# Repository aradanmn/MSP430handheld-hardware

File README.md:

# Handheld MSP430 — Hardware

Hardware design for a DIY handheld game console built around the
**MSP430G2553** microcontroller: bill of materials, breadboard layout, KiCad 9
schematic, and the engineering design history.

This repo is the **hardware side** of the project. The firmware and the
26-lesson MSP430 assembly course that builds it live in the companion
software repo: **[aradanmn/MSP430handheld-firmware](https://github.com/aradanmn/MSP430handheld-firmware)**.

## Components

| Component | Part | Purpose |
|-----------|------|---------|
| MCU | MSP430G2553 (LaunchPad MSP-EXP430G2) | Main controller |
| Display | SSD1325 2.7″ OLED, 128×64 grayscale SPI | Video output |
| SRAM | 23LC1024-I/P (128 KB SPI, DIP-8) | Off-chip framebuffer backing store |
| Flash | W25Q128 (16 MB SPI, DIP breakout, Adafruit #5634) | Asset / level storage |
| Shift register | SN74HC165N (DIP-16) | 8-button input over the SPI bus |
| Audio amp | LM386N-1 (DIP-8) | PWM → speaker |
| Speaker | SP-3605, 8 Ω | Audio output |
| LiPo charger | Adafruit 4410 (USB-C) | Battery charging |
| Battery | Adafruit 2011 (3.7 V LiPo, JST-PH) | Power |

Full ordering detail: [`bom-structured.md`](bom-structured.md),
[`bom-flat.md`](bom-flat.md), [`bom-order.csv`](bom-order.csv).

## Bus & pins

All SPI peripherals share the MSP430's **USCI_B0** bus and are selected by
individual chip-select lines (only one CS low at a time):

| Signal | MSP430 pin |
|--------|-----------|
| SCLK | P1.5 (UCB0CLK) |
| MOSI | P1.7 (UCB0SIMO) |
| MISO | P1.6 (UCB0SOMI) |

The authoritative per-signal chip-select and control assignments (rev 5.0) are
in the schematic `title_block` of
[`schematic/msp430_gameboy.kicad_sch`](schematic/msp430_gameboy.kicad_sch),
and the per-phase wiring is broken out under [`wiring/`](wiring/).

## Repository layout

```
MSP430handheld-hardware/
├── bom-flat.md / bom-structured.md / bom-order.csv   Bill of materials
├── schematic/     KiCad 9 schematic (rev 5.0) + timestamped snapshots
├── breadboard/    Elenco 9440 layout — breadboard_layout.html + breadboard_guide.md
├── scripts/       Schematic generators — gen_kicad7.py (current), gen_kicad6.py (prior)
├── wiring/        Per-build-phase wiring guides (phase-1 … phase-4)
├── DESIGN.md      Handheld rev A: carrier PCB + enclosure design, assumptions to check
├── pcb/           Carrier PCB generator, KiCad board, gerbers/drill/DXF/STEP, DRC report
├── enclosure/     Parametric OpenSCAD enclosure + STLs
├── datasheets/    Component datasheets + pin-function reference (see its README)
├── notes/         Versioned engineering notes (yyyymmdd_HHmmss.md) + SESSION_NOTES.md
└── logs/          Session conversation logs
```

## Build phases

Hardware is added incrementally as the course progresses:

- [`wiring/phase-1-launchpad-only.md`](wiring/phase-1-launchpad-only.md) — bare LaunchPad (Lessons 1–5)
- [`wiring/phase-2-oled-display.md`](wiring/phase-2-oled-display.md) — OLED + SRAM + Flash on the SPI bus
- [`wiring/phase-3-buttons-shift-register.md`](wiring/phase-3-buttons-shift-register.md) — 8-button SN74HC165N input
- [`wiring/phase-4-audio.md`](wiring/phase-4-audio.md) — LM386 amplifier + speaker

## Schematic

The KiCad 9 schematic is generated programmatically rather than drawn by hand.

```bash
python3 scripts/gen_kicad7.py     # writes schematic/msp430_gameboy.kicad_sch
```

Optional validation: `pip install kiutils`.

- **PCB (rev 6.0):** [`schematic/msp430_handheld.kicad_sch`](schematic/msp430_handheld.kicad_sch) / [PDF](schematic/msp430_handheld.pdf), MSP430G2553 on board, written by `scripts/gen_schematic.py` as part of `pcb/build.sh`
- Breadboard (rev 5.0): [`schematic/msp430_gameboy.kicad_sch`](schematic/msp430_gameboy.kicad_sch) — rev 5.0 (adds OLED CS/DC/RST, SRAM, Flash)
- Generator: [`scripts/gen_kicad7.py`](scripts/gen_kicad7.py) (current), `scripts/gen_kicad6.py` (prior)
- Timestamped snapshots are kept alongside the current file for history.

## Design history

The [`notes/`](notes/) and [`logs/`](logs/) directories hold versioned
engineering notes and session logs from the breadboard / rev 4.0 bring-up —
the KiCad 9 format lessons, the grid-alignment debugging that fixed
"nothing connected", component-position tables, and net lists. Preserved
verbatim as design history.

## Status

- [x] BOM (DigiKey, ~$53 core)
- [x] Breadboard layout (Elenco 9440, 4-panel)
- [x] KiCad 9 schematic — rev 5.0 (grid-aligned, connections verified)
- [x] PCB layout: rev A carrier board, routed, DRC clean, **not yet fabricated** ([`DESIGN.md`](DESIGN.md))
- [x] Enclosure: rev A, STLs exported, **not yet printed** ([`DESIGN.md`](DESIGN.md))
- [x] Schematic rev 6.0 for the PCB ([`schematic/msp430_handheld.pdf`](schematic/msp430_handheld.pdf)), generated from the same table as the board and checked against it
- [ ] BOM Rev G with the PCB-build parts

## Authorship

The BOM review, the datasheet index, and the rev A PCB and enclosure
(`DESIGN.md`, `pcb/`, `enclosure/`) were written by Claude (Anthropic's AI
model) working in Claude Code. Scott Dean set the goals, chose the parts,
builds and tests the hardware, and reviews and decides what is merged.

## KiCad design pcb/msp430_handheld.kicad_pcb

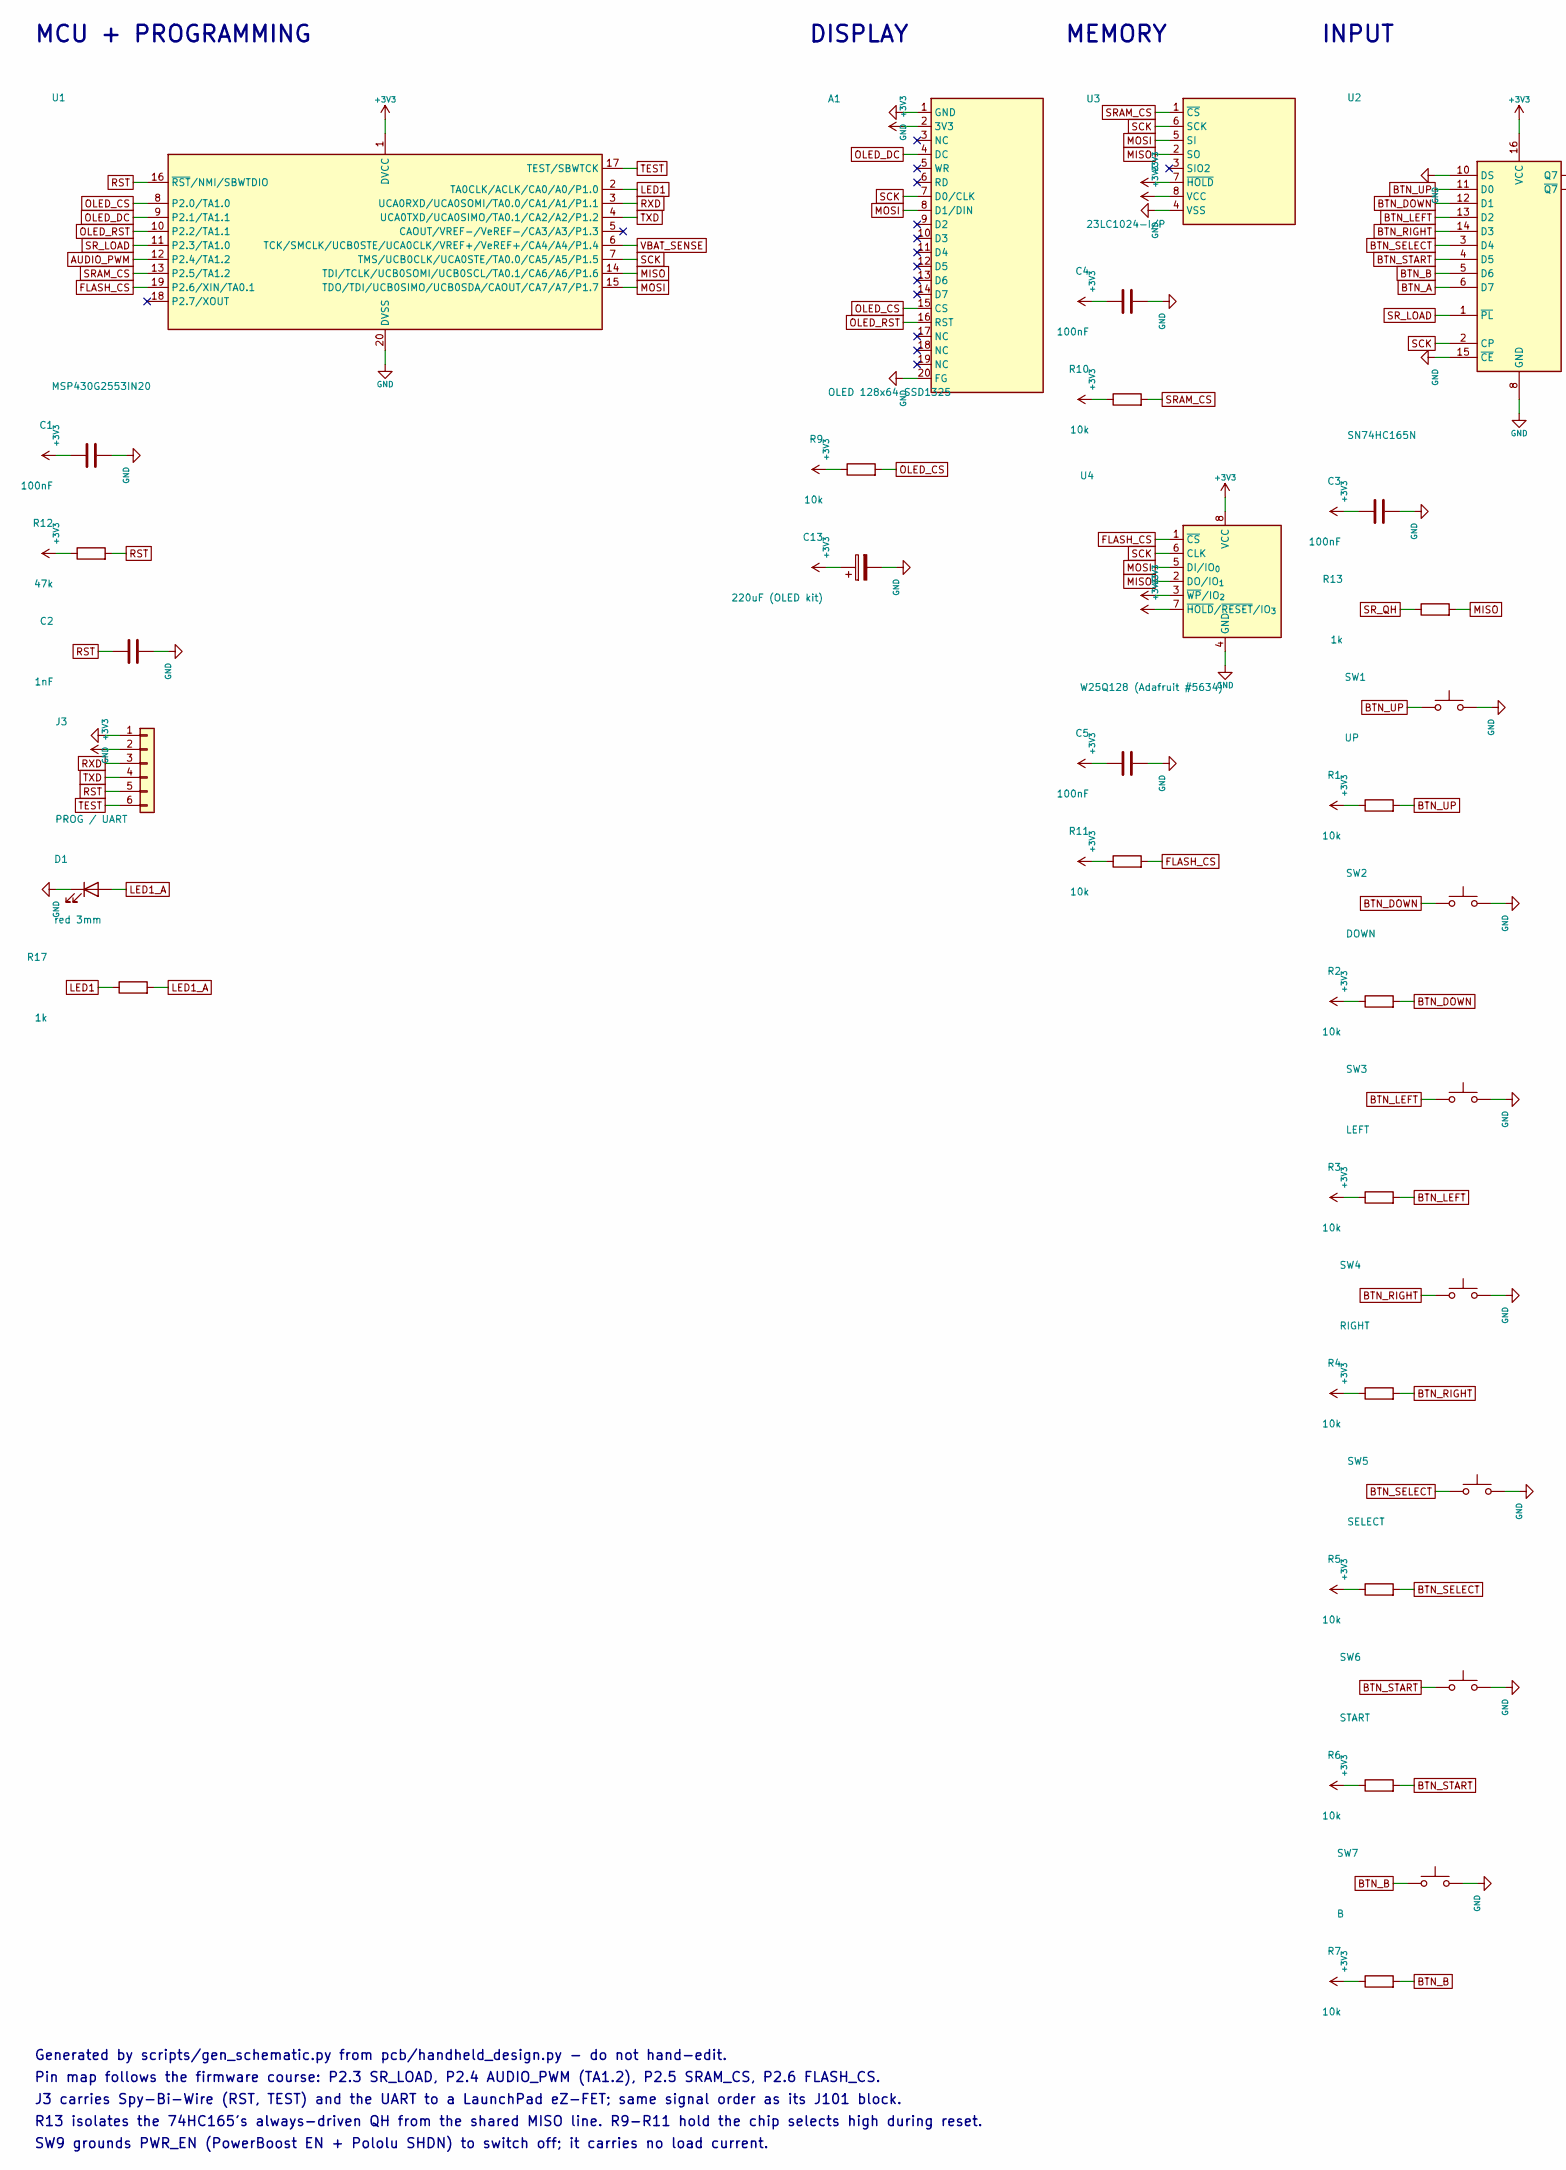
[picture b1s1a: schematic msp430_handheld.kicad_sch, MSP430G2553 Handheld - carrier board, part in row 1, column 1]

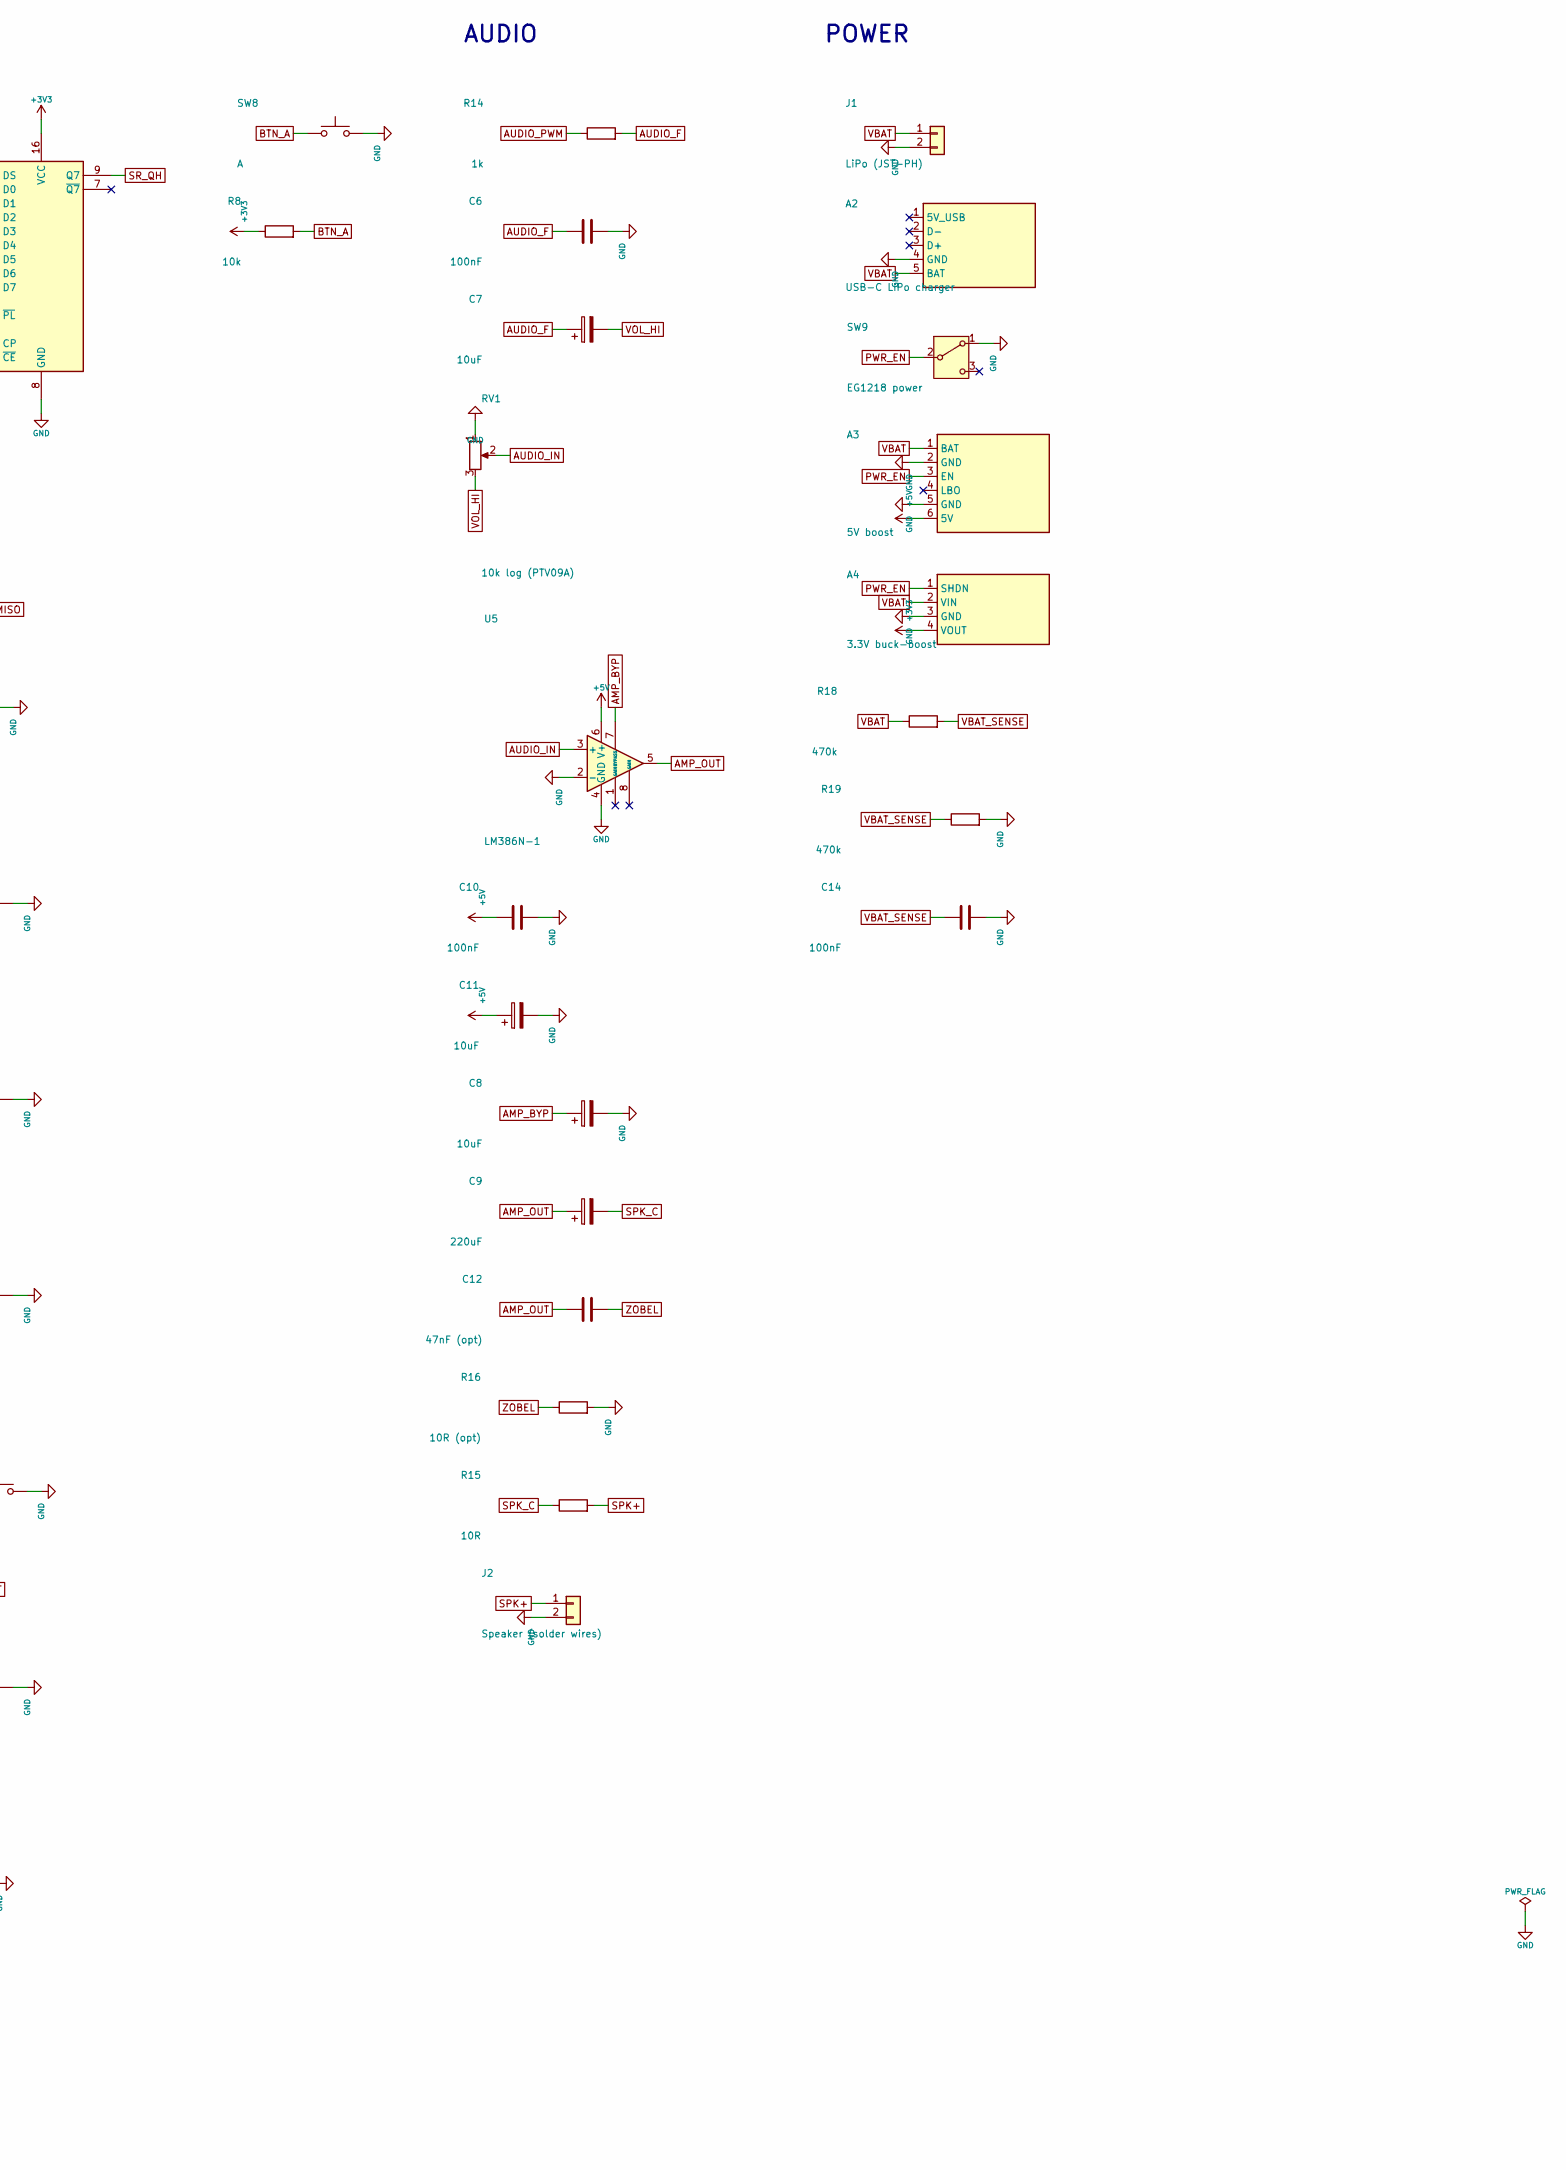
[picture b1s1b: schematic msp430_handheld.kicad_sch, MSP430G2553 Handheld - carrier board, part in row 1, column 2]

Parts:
A1: OLED 128x64 SSD1325; Adafruit_2674_OLED_2.7in
A2: USB-C LiPo charger; Adafruit_4410_USBC_LiPo
A3: 5V boost; Adafruit_1903_PowerBoost500
A4: 3.3V buck-boost; Pololu_S7V8F3
C1, C3, C4, C5, C6, C10, C14: 100nF; C_Disc_D3.0mm_W1.6mm_P2.50mm
C2: 1nF; C_Disc_D3.0mm_W1.6mm_P2.50mm
C7, C8, C11: 10uF; CP_Radial_D5.0mm_P2.00mm
C9: 220uF; CP_Radial_D6.3mm_P2.50mm
C12: 47nF (opt); C_Disc_D3.0mm_W1.6mm_P2.50mm
C13: 220uF (OLED kit); CP_Radial_D6.3mm_P2.50mm
D1: red 3mm; LED_D3.0mm
J1: LiPo (JST-PH); JST_PH_S2B-PH-K_1x02_P2.00mm_Horizontal
J2: Speaker (solder wires); PinHeader_1x02_P2.54mm_Vertical
J3: PROG / UART; PinHeader_1x06_P2.54mm_Horizontal
R1, R2, R3, R4, R5, R6, R7, R8, R9, R10, R11: 10k; R_Axial_DIN0207_L6.3mm_D2.5mm_P7.62mm_Horizontal
R12: 47k; R_Axial_DIN0207_L6.3mm_D2.5mm_P7.62mm_Horizontal
R13, R14, R17: 1k; R_Axial_DIN0207_L6.3mm_D2.5mm_P7.62mm_Horizontal
R15: 10R; R_Axial_DIN0207_L6.3mm_D2.5mm_P7.62mm_Horizontal
R16: 10R (opt); R_Axial_DIN0207_L6.3mm_D2.5mm_P7.62mm_Horizontal
R18, R19: 470k; R_Axial_DIN0207_L6.3mm_D2.5mm_P7.62mm_Horizontal
RV1: 10k log (PTV09A); Potentiometer_Bourns_PTV09A-1_Single_Vertical
SW1: UP; SW_TH_Tactile_Omron_B3F-100x
SW2: DOWN; SW_TH_Tactile_Omron_B3F-100x
SW3: LEFT; SW_TH_Tactile_Omron_B3F-100x
SW4: RIGHT; SW_TH_Tactile_Omron_B3F-100x
SW5: SELECT; SW_TH_Tactile_Omron_B3F-100x
SW6: START; SW_TH_Tactile_Omron_B3F-100x
SW7: B; SW_TH_Tactile_Omron_B3F-100x
SW8: A; SW_TH_Tactile_Omron_B3F-100x
SW9: EG1218 power; SW_E-Switch_EG1218
U1: MSP430G2553IN20; DIP-20_W7.62mm_Socket
U2: SN74HC165N; DIP-16_W7.62mm
U3: 23LC1024-I/P; DIP-8_W7.62mm
U4: W25Q128 (Adafruit #5634); DIP-8_W7.62mm
U5: LM386N-1; DIP-8_W7.62mm

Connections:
+3V3: A1.2 (3V3), A4.4 (VOUT), C1.1, C3.1, C4.1, C5.1, C13.1, J3.2, R1.1, R2.1, R3.1, R4.1, R5.1, R6.1, R7.1, R8.1, R9.1, R10.1, R11.1, R12.1, U1.1 (DVCC), U2.16 (VCC), U3.7 (~HOLD), U3.8 (VCC), U4.3 (~WP/IO_{2}), U4.7 (~HOLD/~RESET/IO_{3}), U4.8 (VCC)
+5V: A3.6 (5V), C10.1, C11.1, U5.6 (V+)
AMP_BYP: C8.1, U5.7 (BYPASS)
AMP_OUT: C9.1, C12.1, U5.5
AUDIO_F: C6.1, C7.1, R14.2
AUDIO_IN: RV1.2, U5.3 (+)
AUDIO_PWM: R14.1, U1.12 (P2.4/TA1.2)
BTN_A: R8.2, SW8.1, U2.6 (D7)
BTN_B: R7.2, SW7.1, U2.5 (D6)
BTN_DOWN: R2.2, SW2.1, U2.12 (D1)
BTN_LEFT: R3.2, SW3.1, U2.13 (D2)
BTN_RIGHT: R4.2, SW4.1, U2.14 (D3)
BTN_SELECT: R5.2, SW5.1, U2.3 (D4)
BTN_START: R6.2, SW6.1, U2.4 (D5)
BTN_UP: R1.2, SW1.1, U2.11 (D0)
FLASH_CS: R11.2, U1.19 (P2.6/XIN/TA0.1), U4.1 (~CS)
GND: A1.1 (GND), A1.20 (FG), A2.4 (GND), A3.2 (GND), A3.5 (GND), A4.3 (GND), C1.2, C2.2, C3.2, C4.2, C5.2, C6.2, C8.2, C10.2, C11.2, C13.2, C14.2, D1.1 (K), J1.2, J2.2, J3.1, R16.2, R19.2, RV1.1, SW1.2, SW2.2, SW3.2, SW4.2, SW5.2, SW6.2, SW7.2, SW8.2, SW9.1 (A), U1.20 (DVSS), U2.8 (GND), U2.10 (DS), U2.15 (~CE), U3.4 (VSS), U4.4 (GND), U5.2 (-), U5.4 (GND)
LED1: R17.1, U1.2 (TA0CLK/ACLK/CA0/A0/P1.0)
LED1_A: D1.2 (A), R17.2
MISO: R13.2, U1.14 (TDI/TCLK/UCB0SOMI/UCB0SCL/TA0.1/CA6/A6/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), U3.2 (SO), U4.2 (DO/IO_{1})
MOSI: A1.8 (D1/DIN), U1.15 (TDO/TDI/UCB0SIMO/UCB0SDA/CAOUT/CA7/A7/P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), U3.5 (SI), U4.5 (DI/IO_{0})
OLED_CS: A1.15 (CS), R9.2, U1.8 (P2.0/TA1.0)
OLED_DC: A1.4 (DC), U1.9 (P2.1/TA1.1)
OLED_RST: A1.16 (RST), U1.10 (P2.2/TA1.1)
PWR_EN: A3.3 (EN), A4.1 (SHDN), SW9.2 (B)
RST: C2.1, J3.5, R12.2, U1.16 (~RST/NMI/SBWTDIO)
RXD: J3.3, U1.3 (UCA0RXD/UCA0SOMI/TA0.0/CA1/A1/P1.1)
SCK: A1.7 (D0/CLK), U1.7 (TMS/UCB0CLK/UCA0STE/TA0.0/CA5/A5/P1.5), U2.2 (CP), U3.6 (SCK), U4.6 (CLK)
SPK+: J2.1, R15.2
SPK_C: C9.2, R15.1
SRAM_CS: R10.2, U1.13 (P2.5/TA1.2), U3.1 (~CS)
SR_LOAD: U1.11 (P2.3/TA1.0), U2.1 (~PL)
SR_QH: R13.1, U2.9 (Q7)
TEST: J3.6, U1.17 (TEST/SBWTCK)
TXD: J3.4, U1.4 (UCA0TXD/UCA0SIMO/TA0.1/CA2/A2/P1.2)
VBAT: A2.5 (BAT), A3.1 (BAT), A4.2 (VIN), J1.1, R18.1
VBAT_SENSE: C14.1, R18.2, R19.1, U1.6 (TCK/SMCLK/UCB0STE/UCA0CLK/VREF+/VeREF+/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)
VOL_HI: C7.2, RV1.3
ZOBEL: C12.2, R16.1

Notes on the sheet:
MCU + PROGRAMMING
DISPLAY
MEMORY
INPUT
AUDIO
POWER
Generated by scripts/gen_schematic.py from pcb/handheld_design.py - do not hand-edit.
Pin map follows the firmware course: P2.3 SR_LOAD, P2.4 AUDIO_PWM (TA1.2), P2.5 SRAM_CS, P2.6 FLASH_CS.
J3 carries Spy-Bi-Wire (RST, TEST) and the UART to a LaunchPad eZ-FET; same signal order as its J101 block.
R13 isolates the 74HC165's always-driven QH from the shared MISO line. R9-R11 hold the chip selects high during reset.
SW9 grounds PWR_EN (PowerBoost EN + Pololu SHDN) to switch off; it carries no load current.

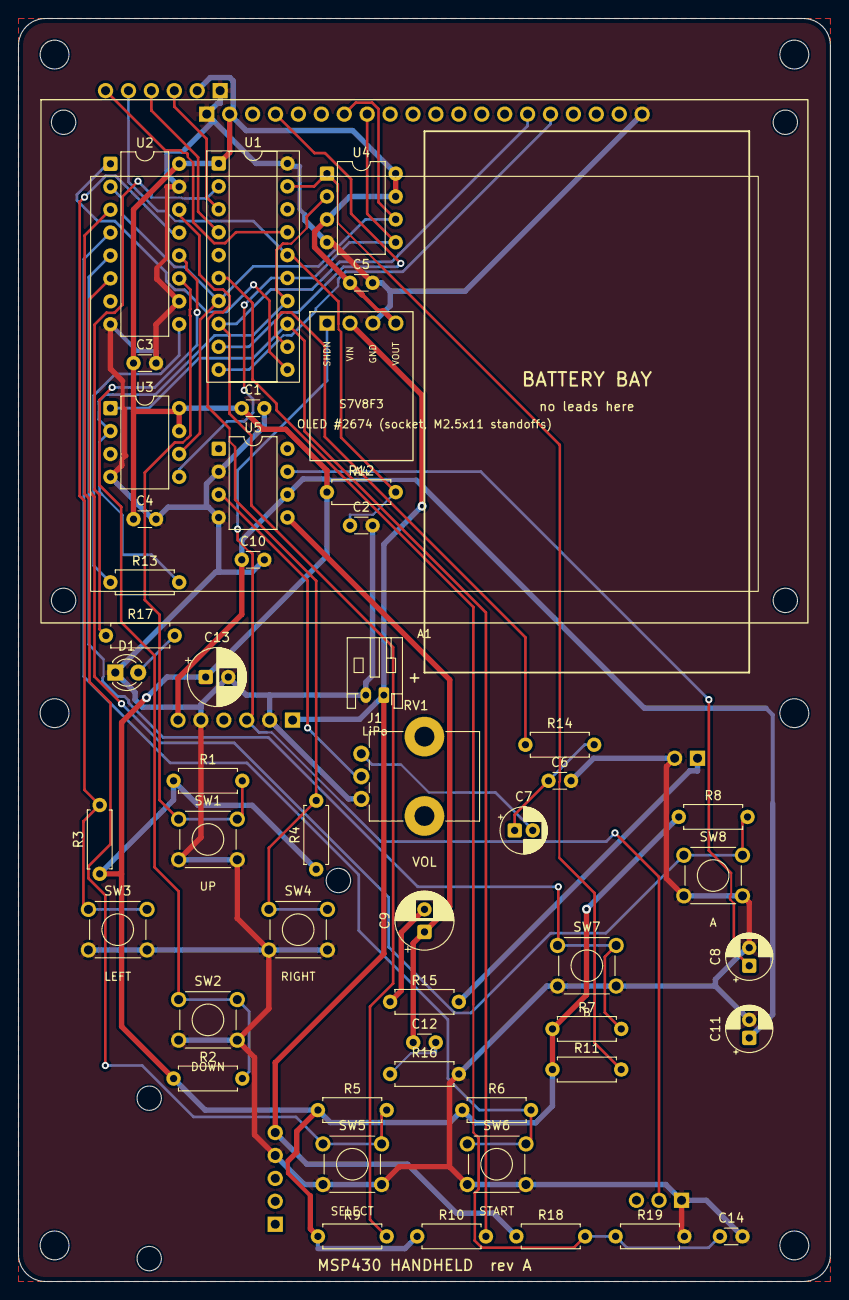
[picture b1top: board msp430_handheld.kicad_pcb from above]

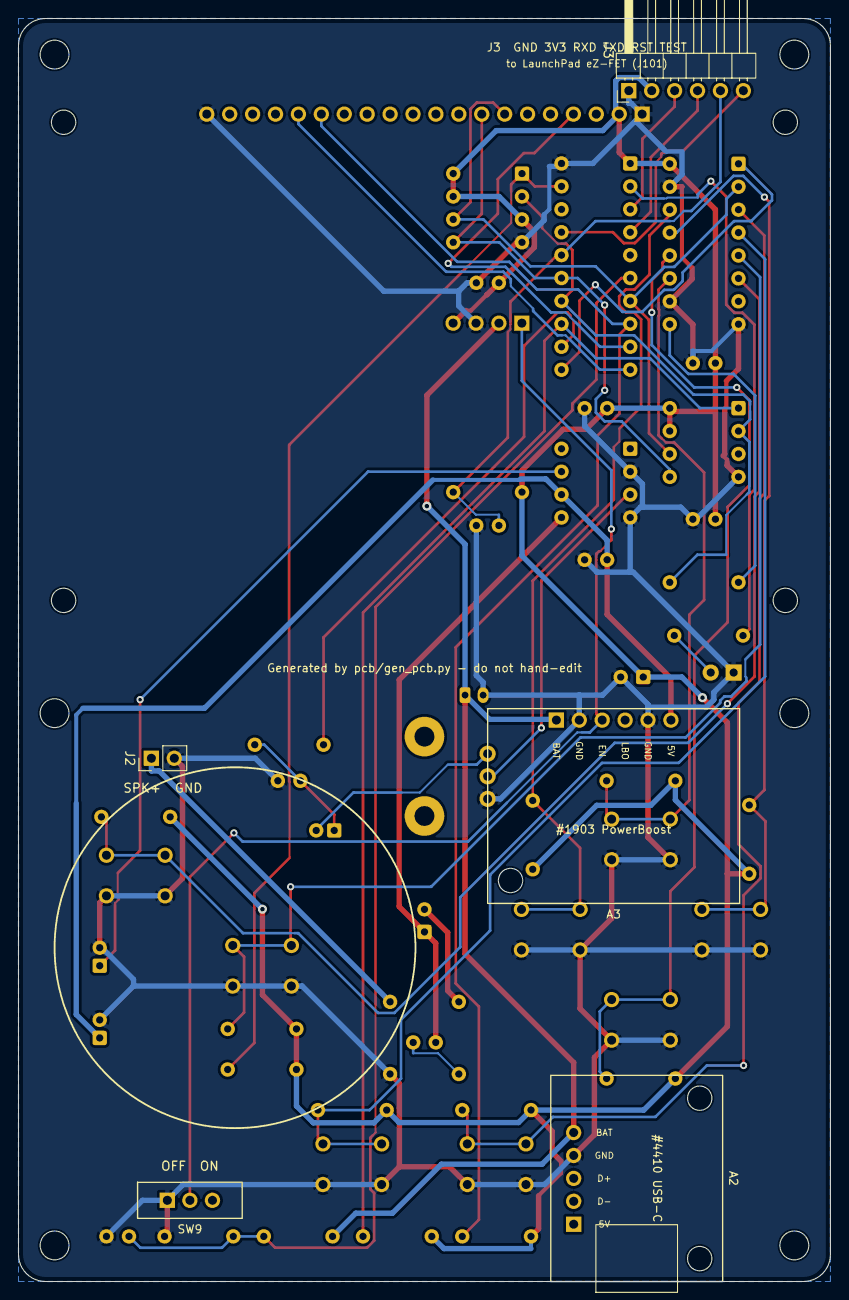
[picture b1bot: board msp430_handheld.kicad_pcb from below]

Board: 2 copper layers, 90.0 x 140.0 mm, 62 parts (5 on the bottom side), 39 nets.

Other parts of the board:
H1, H2, H3, H4, H5, H6: MountingHole_3.2mm_M3

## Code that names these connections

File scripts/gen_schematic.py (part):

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    body.append(power("power:GND", "GND", fx, fy + G))
    notes = [
        "Generated by scripts/gen_schematic.py from pcb/handheld_design.py - do not hand-edit.",
        "Pin map follows the firmware course: P2.3 SR_LOAD, P2.4 AUDIO_PWM (TA1.2), P2.5 SRAM_CS, P2.6 FLASH_CS.",
        "J3 carries Spy-Bi-Wire (RST, TEST) and the UART to a LaunchPad eZ-FET; same signal order as its J101 block.",
        "R13 isolates the 74HC165's always-driven QH from the shared MISO line. R9-R11 hold the chip selects high during reset.",
        "SW9 grounds PWR_EN (PowerBoost EN + Pololu SHDN) to switch off; it carries no load current.",
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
